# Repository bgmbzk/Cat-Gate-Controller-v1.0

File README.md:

# Cat-Gate Controller v1.0 🐱🚪

Bu proje, kedilerin sesli komutlarına (veya belirli miyavlama frekanslarına) duyarlı bir şekilde çalışan, otomatik bir kedi kapısı kontrol sistemidir. Donanım tasarımı tamamen **KiCad** kullanılarak gerçekleştirilmiştir.

## 🎯 Projenin Amacı
Projenin temel amacı, evcil hayvanların eve giriş ve çıkış süreçlerini otomatize ederek hem konforu hem de güvenliği artırmaktır. Sistem, bir mikrofon sensöründen gelen verileri işleyerek **DRV8833** motor sürücüsü üzerinden kapı mekanizmasını harekete geçirir.

## 🛠 Teknik Özellikler ve Tasarım Süreci
Bu tasarımda **ATmega328P** mikrodenetleyici kullanılmıştır. Tasarım süreci boyunca sadece bir devre kurmayı değil, aynı zamanda yüksek akım çeken bileşenlerin bir sistem üzerindeki etkilerini yönetmeyi öğrendik.

### 🚀 Kritik Tasarım Noktaları & Kazanımlar
Projede özellikle motorun elektriksel gerekliliklerini yerine getirmek adına şu teknik detaylara odaklanılmıştır:

* **Yüksek Akım ve Kalın Yollar:** Motorun çalışma anında çektiği yüksek akım (inrush current) nedeniyle, güç hatlarını (VCC ve GND) standart sinyal yollarından çok daha **kalın** tutarak voltaj düşümlerini ve ısınmayı engelledik.
* **Gürültü Yönetimi:** Motorların devreye girerken oluşturduğu elektriksel gürültünün (noise) hassas mikrodenetleyici sinyallerini bozmaması için **Ground Plane (Toprak Düzlemi)** stratejisi uygulanmıştır.
* **Katman Yönetimi:** Kartın her iki yüzünde de (F.Cu ve B.Cu) geniş bakır alanlar oluşturularak hem gürültü kalkanı sağlanmış hem de termal rahatlama (soğutma) elde edilmiştir.

## 📸 Proje Görselleri

### 1. Devre Şematiği (Schematic)
Sistemin mantıksal bağlantılarını ve bileşenler arası iletişimi temsil eder.

### 2. PCB Tasarımı (Layout)
Güç yollarının kalınlığına ve gürültü kalkanına dikkat edilen baskı devre yerleşimi.

### 3. 3D Model Önizlemesi
Donanımın fiziksel olarak bitmiş halinin 3D render görüntüsü.

## 📁 Dosya Yapısı
* `/Production`: Fabrika üretimi için gerekli olan Gerber ve Drill (.drl) dosyaları.
* `/Source`: KiCad proje dosyaları (.kicad_pro, .kicad_sch, .kicad_pcb).

---
*Bu proje, gömülü sistemler ve donanım tasarımı konusundaki öğrenim sürecinin bir parçası olarak geliştirilmiştir.*

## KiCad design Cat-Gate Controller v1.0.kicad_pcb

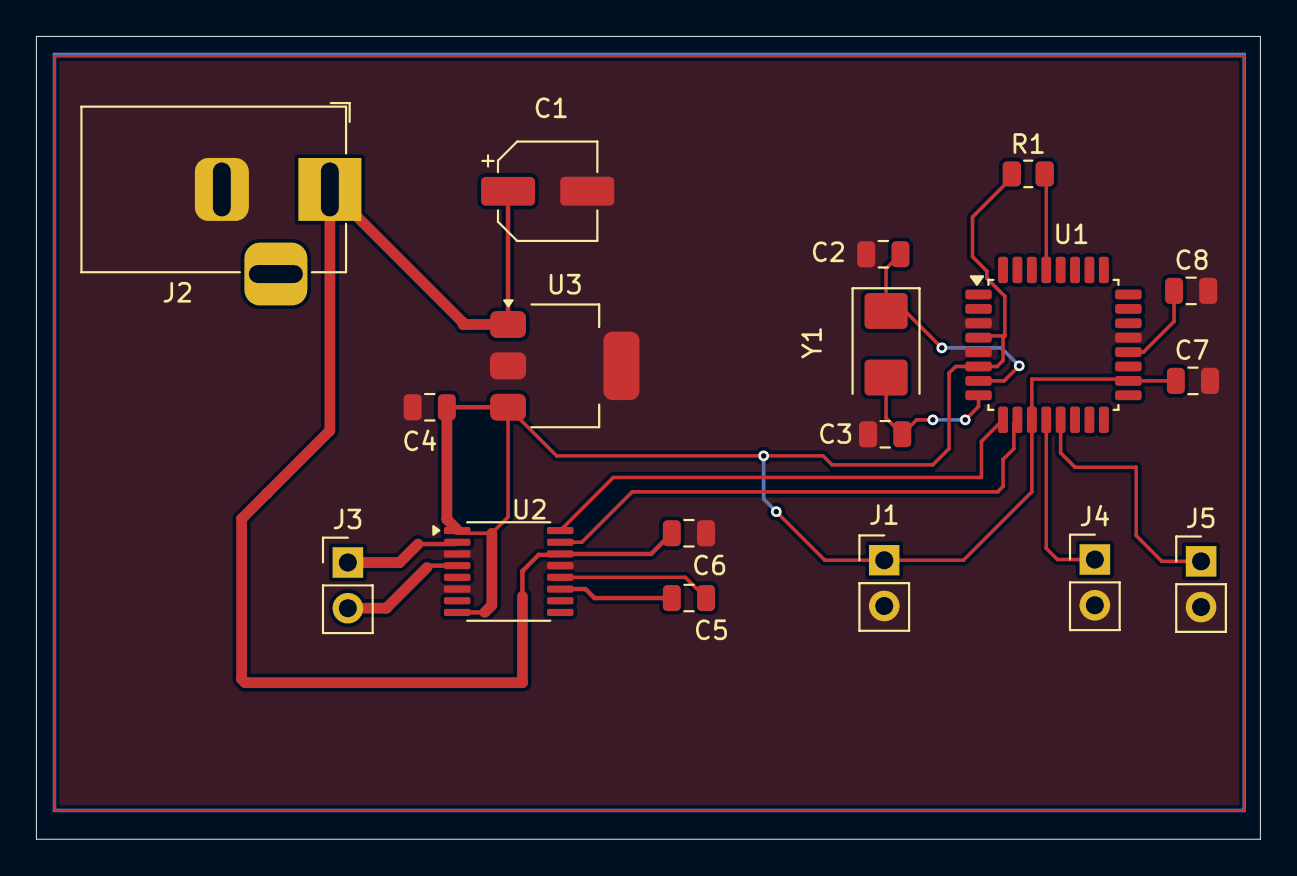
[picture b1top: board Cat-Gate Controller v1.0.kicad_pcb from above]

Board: 2 copper layers, 68.0 x 44.6 mm, 18 parts (0 on the bottom side), 15 nets.

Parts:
C1: C_Polarized; CP_Elec_5x5.4
C2, C3: 22pF; C_0805_2012Metric
C4: C; C_0805_2012Metric
C5: 10nF; C_0805_2012Metric
C6: 2.2uF; C_0805_2012Metric
C7, C8: 100nF; C_0805_2012Metric
J1: Conn_01x03; PinHeader_1x02_P2.54mm_Vertical
J2: Barrel_Jack; BarrelJack_Horizontal
J3, J4, J5: Conn_01x02; PinHeader_1x02_P2.54mm_Vertical
R1: 10kΩ; R_0805_2012Metric
U1: ATmega328P-A; TQFP-32_7x7mm_P0.8mm
U2: DRV8833PW; TSSOP-16_4.4x5mm_P0.65mm
U3: L7805; SOT-223-3_TabPin2
Y1: Crystal; Crystal_SMD_5032-2Pin_5.0x3.2mm

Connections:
GND: C1.2, C2.1, C3.1, C4.2, C6.2, C7.2, C8.2, J1.2, J2.2, J4.2, J5.2, U1.3 (GND), U1.5 (GND), U1.21 (GND), U2.3 (AISEN), U2.6 (BISEN), U2.13 (GND), U3.2 (GND)
unnamed: C4.1, C7.1, J1.1, R1.1, U1.4 (VCC), U1.6 (VCC), U1.11 (PD7), U1.18 (AVCC), U2.1 (~SLEEP), U2.8 (~FAULT), U3.3 (OUT)
unnamed: J3.1, U2.2 (AOUT1)
unnamed: J3.2, U2.4 (AOUT2)
unnamed: J4.1, U1.12 (PB0)
unnamed: J5.1, U1.13 (PB1)
unnamed: C8.1, U1.20 (AREF)
unnamed: U1.9 (PD5), U2.16 (AIN1)
unnamed: U1.10 (PD6), U2.15 (AIN2)
unnamed: C2.2, U1.7 (XTAL1/PB6), Y1.1
unnamed: C3.2, U1.8 (XTAL2/PB7), Y1.2
unnamed: R1.2, U1.29 (~RESET/PC6)
unnamed: C5.1, U2.11 (VCP)
unnamed: C1.1, C6.1, J2.1, U2.14 (VINT), U3.1 (IN)
unnamed: C5.2, U2.12 (VM)

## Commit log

2026-04-21 Add README for Cat-Gate Controller project
    This README provides an overview of the Cat-Gate Controller project, including its purpose, technical specifications, design process, and visual representations.
